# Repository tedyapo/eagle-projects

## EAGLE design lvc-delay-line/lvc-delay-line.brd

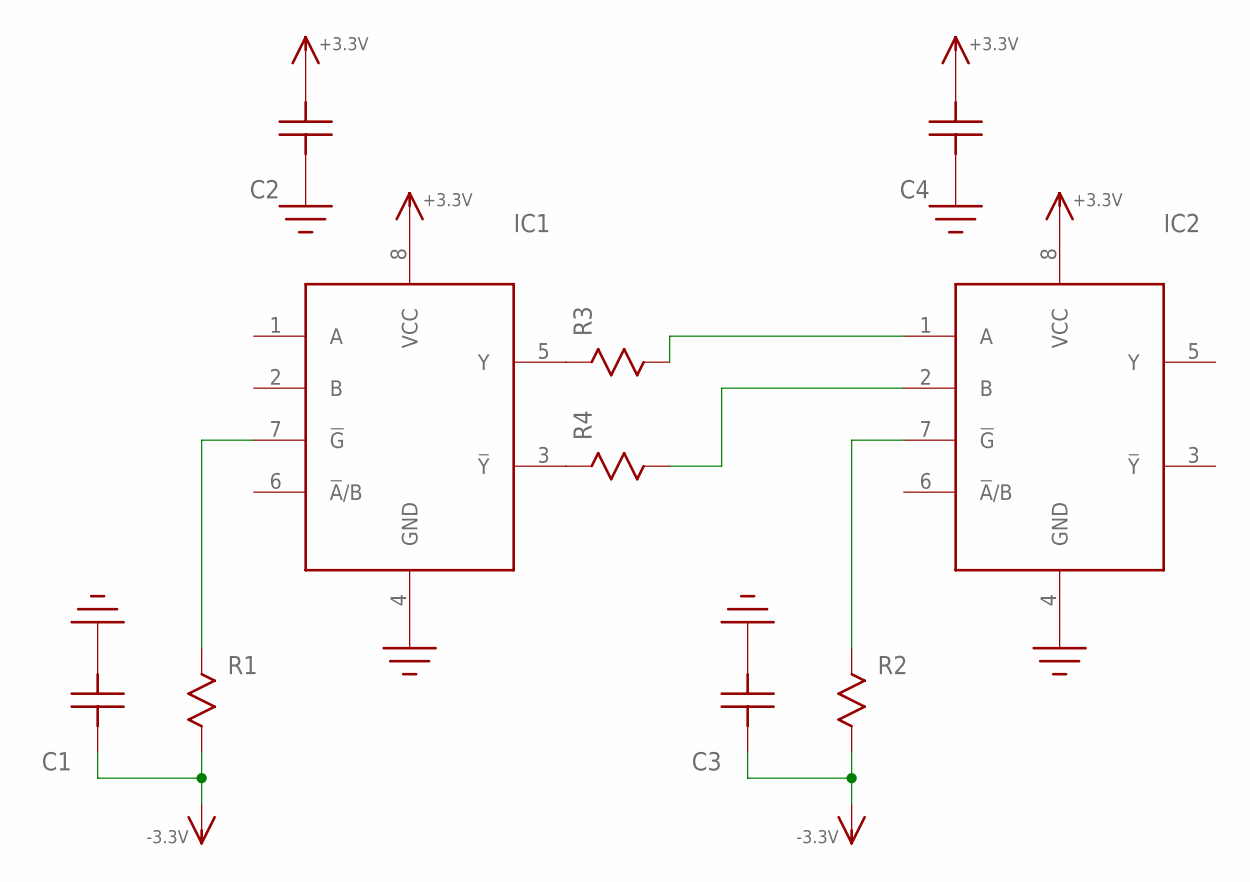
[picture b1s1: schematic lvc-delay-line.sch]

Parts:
C1, C2, C3, C4: C0603
IC1, IC2: 74LVC2G157; SSOP8
R1, R2: R0603
R3, R4: R0402; 0402

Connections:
+3.3V: C2.P$1, C4.P$1, IC1.8 (VCC), IC2.8 (VCC)
-3.3V: C1.P$2, C3.P$2, R1.P$2, R2.P$2
GND: C1.P$1, C2.P$2, C3.P$1, C4.P$2, IC1.4 (GND), IC2.4 (GND)
unnamed: IC1.7 (!G!), R1.P$1
unnamed: IC2.7 (!G!), R2.P$1
unnamed: IC2.1 (A), R3.2
unnamed: IC2.2 (B), R4.2
unnamed: IC1.5 (Y), R3.1
unnamed: IC1.3 (!Y!), R4.1

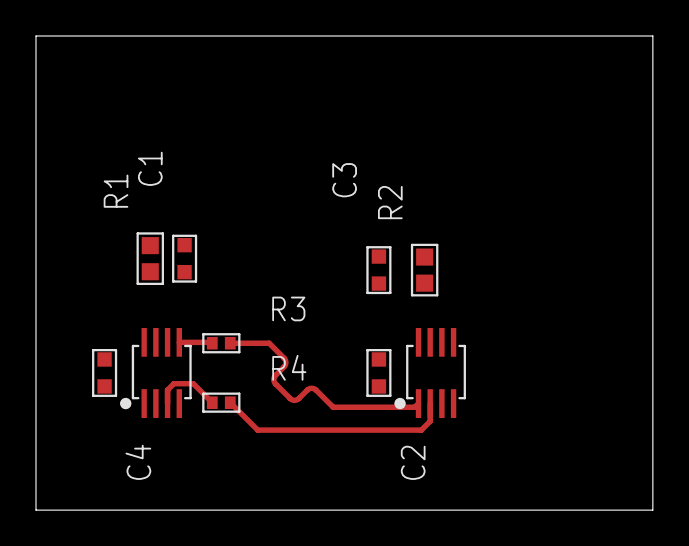
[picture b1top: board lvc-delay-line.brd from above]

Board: 2 copper layers, 34.3 x 26.3 mm, 10 parts (0 on the bottom side), 9 nets.

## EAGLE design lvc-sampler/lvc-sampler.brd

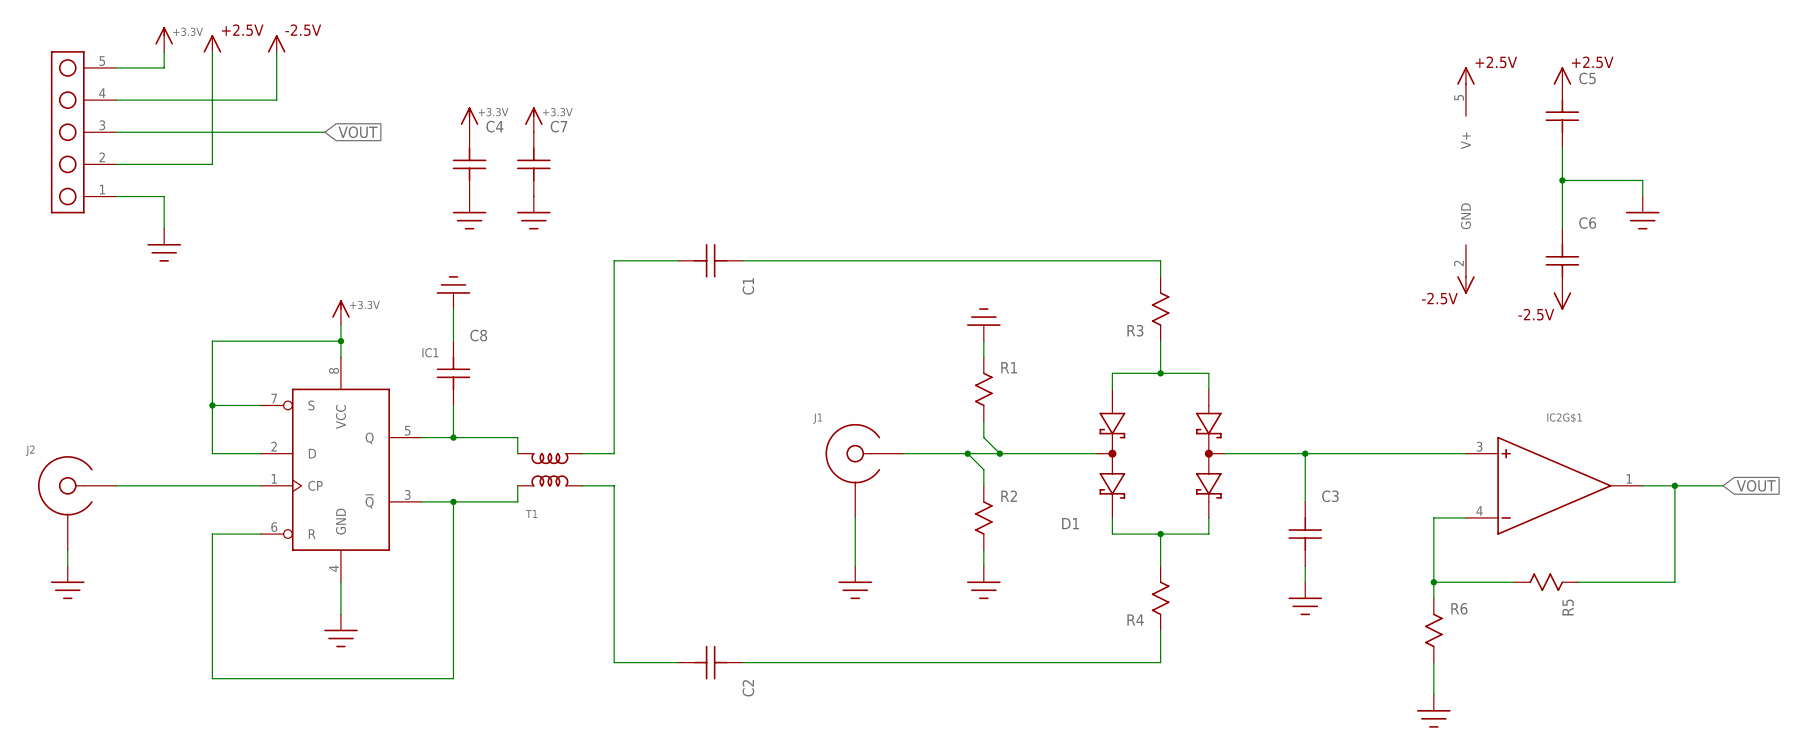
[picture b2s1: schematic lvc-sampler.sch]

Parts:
C1, C2, C3, C4, C5, C6, C7, C8: C0603
D1: SMS3923-081; SC-88
IC1: 74LVC2G74; SSOP8
IC2: MCP601; SOT23-5
J1, J2: SMA-EDGE-LAUNCH4020_TAPER; SMA_EDGE_LAUNCH_2L_4020_TAPER
J3: HEADER_5PIN
R1, R2, R3, R4, R5, R6: R0603
T1: MABA007159; MABAES0061

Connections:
+2.5V: C5.P$2, IC2.5 (V+), J3.2
+3.3V: C4.P$2, C7.P$2, IC1.2 (D), IC1.7 (S), IC1.8 (VCC), J3.5
-2.5V: C6.P$1, IC2.2 (GND), J3.4
GND: C3.P$1, C4.P$1, C5.P$1, C6.P$2, C7.P$1, C8.P$2, IC1.4 (GND), J1.BOTTOM_GND (SHIELD), J1.GND@1 (SHIELD), J1.GND@2 (SHIELD), J1.GND@3 (SHIELD), J1.GND@4 (SHIELD), J1.GND@5 (SHIELD), J1.GND@6 (SHIELD), J1.GND@7 (SHIELD), J1.GND@8 (SHIELD), J1.GND@14 (SHIELD), J1.GND@15 (SHIELD), J1.GND@16 (SHIELD), J1.GND@17 (SHIELD), J1.GND_PAD1 (SHIELD), J1.GND_PAD2 (SHIELD), J1.P$1 (SHIELD), J1.P$2 (SHIELD), J2.BOTTOM_GND (SHIELD), J2.GND@1 (SHIELD), J2.GND@2 (SHIELD), J2.GND@3 (SHIELD), J2.GND@4 (SHIELD), J2.GND@5 (SHIELD), J2.GND@6 (SHIELD), J2.GND@7 (SHIELD), J2.GND@8 (SHIELD), J2.GND@14 (SHIELD), J2.GND@15 (SHIELD), J2.GND@16 (SHIELD), J2.GND@17 (SHIELD), J2.GND_PAD1 (SHIELD), J2.GND_PAD2 (SHIELD), J2.P$1 (SHIELD), J2.P$2 (SHIELD), J3.1, R1.P$1, R2.P$2, R6.P$2
unnamed: IC1.3 (!Q!), IC1.6 (R), T1.5
unnamed: D1.2 (COMMON0), J1.CENTER@1 (CENTER), R1.P$2, R2.P$1
unnamed: D1.1 (ANODE0), D1.6 (ANODE1), R3.P$1
unnamed: D1.3 (CATHODE0), D1.4 (CATHODE1), R4.P$2
unnamed: C1.P$2, R3.P$2
unnamed: C2.P$2, R4.P$1
unnamed: C1.P$1, T1.3
unnamed: C2.P$1, T1.1
unnamed: C8.P$1, IC1.5 (Q), T1.4
unnamed: IC1.1 (CP), J2.CENTER@1 (CENTER)
unnamed: C3.P$2, D1.5 (COMMON1), IC2.3 (+)
unnamed: IC2.4 (-), R5.P$2, R6.P$1
VOUT: IC2.1 (OUT), J3.3, R5.P$1

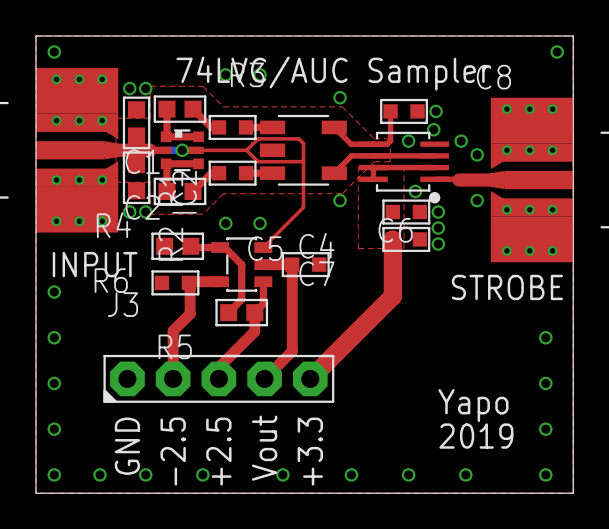
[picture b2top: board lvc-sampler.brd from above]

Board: 2 copper layers, 29.8 x 25.4 mm, 21 parts (1 on the bottom side), 17 nets.

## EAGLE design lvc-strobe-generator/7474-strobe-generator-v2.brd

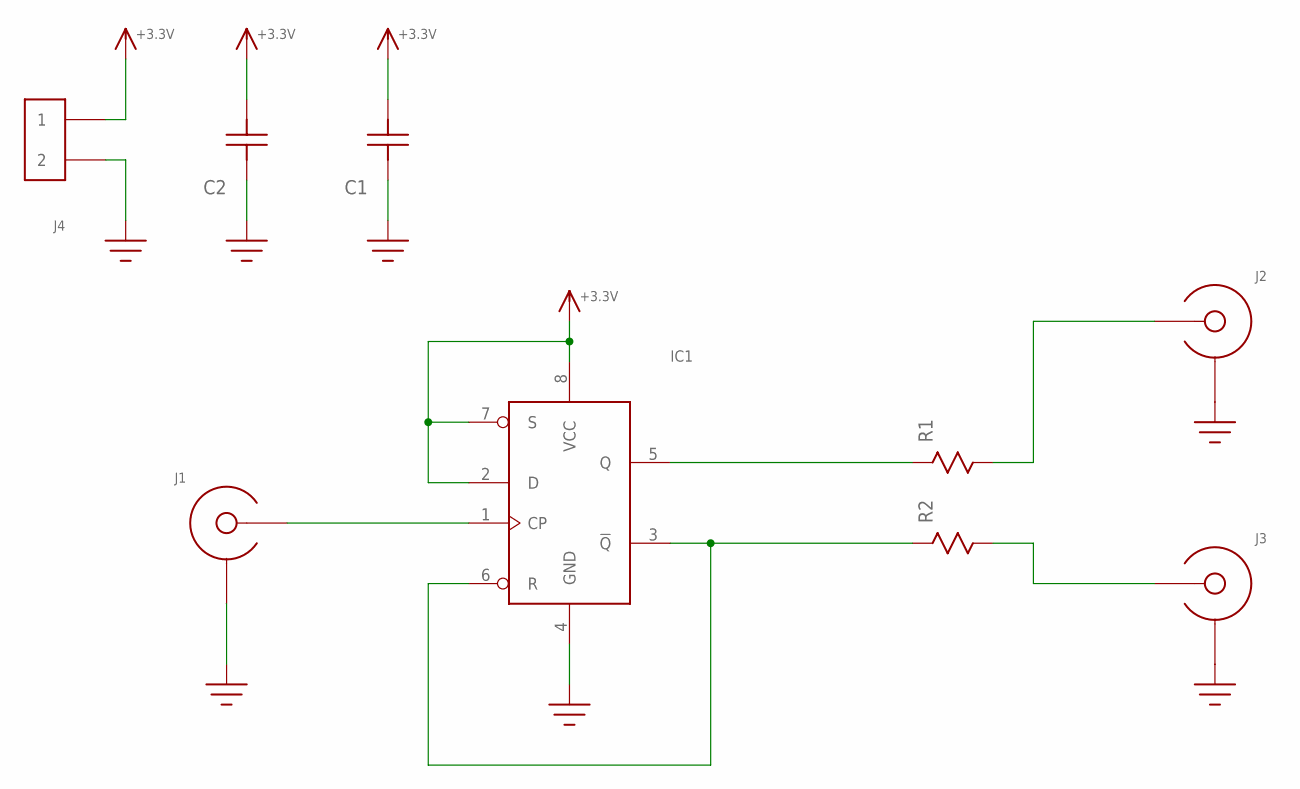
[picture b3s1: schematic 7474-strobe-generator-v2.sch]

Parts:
C1: C0603
C2: C1206; 1206
IC1: 74LVC2G74; SSOP8
J1, J2, J3: SMA-EDGE-LAUNCH4020_TAPER; SMA_EDGE_LAUNCH_2L_4020_TAPER
J4: HEADER_2PIN
R1, R2: R0603

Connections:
+3.3V: C1.P$1, C2.P$1, IC1.2 (D), IC1.7 (S), IC1.8 (VCC), J4.1
GND: C1.P$2, C2.P$2, IC1.4 (GND), J1.BOTTOM_GND (SHIELD), J1.GND@1 (SHIELD), J1.GND@2 (SHIELD), J1.GND@3 (SHIELD), J1.GND@4 (SHIELD), J1.GND@5 (SHIELD), J1.GND@6 (SHIELD), J1.GND@7 (SHIELD), J1.GND@8 (SHIELD), J1.GND@14 (SHIELD), J1.GND@15 (SHIELD), J1.GND@16 (SHIELD), J1.GND@17 (SHIELD), J1.GND_PAD1 (SHIELD), J1.GND_PAD2 (SHIELD), J1.P$1 (SHIELD), J1.P$2 (SHIELD), J2.BOTTOM_GND (SHIELD), J2.GND@1 (SHIELD), J2.GND@2 (SHIELD), J2.GND@3 (SHIELD), J2.GND@4 (SHIELD), J2.GND@5 (SHIELD), J2.GND@6 (SHIELD), J2.GND@7 (SHIELD), J2.GND@8 (SHIELD), J2.GND@14 (SHIELD), J2.GND@15 (SHIELD), J2.GND@16 (SHIELD), J2.GND@17 (SHIELD), J2.GND_PAD1 (SHIELD), J2.GND_PAD2 (SHIELD), J2.P$1 (SHIELD), J2.P$2 (SHIELD), J3.BOTTOM_GND (SHIELD), J3.GND@1 (SHIELD), J3.GND@2 (SHIELD), J3.GND@3 (SHIELD), J3.GND@4 (SHIELD), J3.GND@5 (SHIELD), J3.GND@6 (SHIELD), J3.GND@7 (SHIELD), J3.GND@8 (SHIELD), J3.GND@14 (SHIELD), J3.GND@15 (SHIELD), J3.GND@16 (SHIELD), J3.GND@17 (SHIELD), J3.GND_PAD1 (SHIELD), J3.GND_PAD2 (SHIELD), J3.P$1 (SHIELD), J3.P$2 (SHIELD), J4.2
unnamed: IC1.1 (CP), J1.CENTER@1 (CENTER)
unnamed: IC1.3 (!Q!), IC1.6 (R), R2.P$1
unnamed: J2.CENTER@1 (CENTER), R1.P$2
unnamed: IC1.5 (Q), R1.P$1
unnamed: J3.CENTER@1 (CENTER), R2.P$2

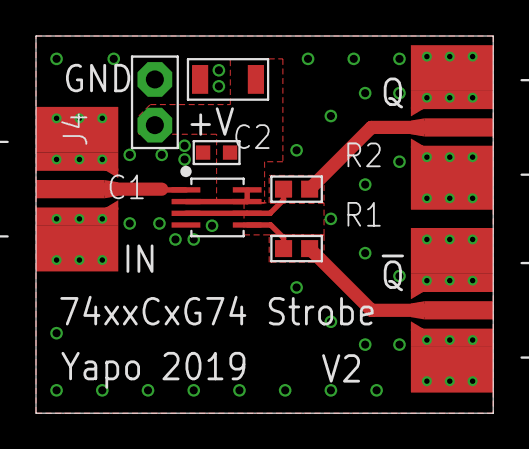
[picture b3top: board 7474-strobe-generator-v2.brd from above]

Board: 2 copper layers, 25.4 x 21.0 mm, 9 parts (0 on the bottom side), 7 nets.

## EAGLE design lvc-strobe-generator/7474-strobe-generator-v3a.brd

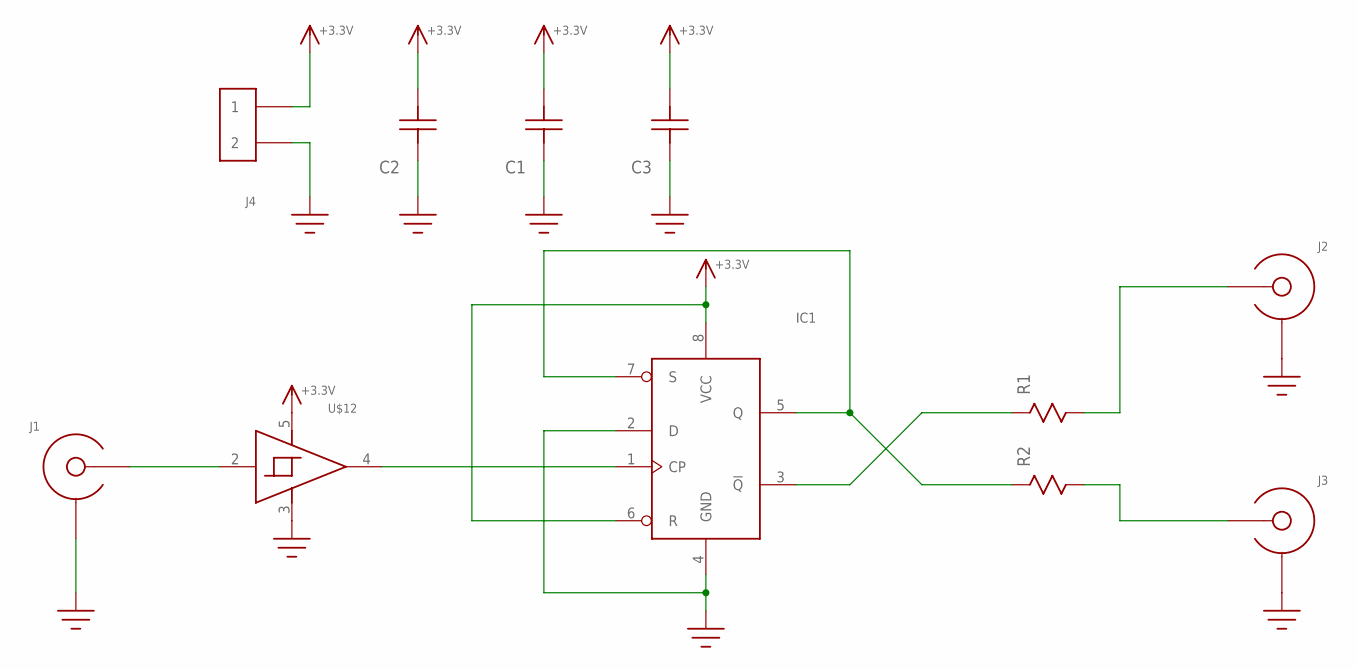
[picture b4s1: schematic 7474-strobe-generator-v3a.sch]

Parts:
C1, C3: C0603
C2: C1206; 1206
IC1: 74LVC2G74; SSOP8
J1, J2, J3: SMA-EDGE-LAUNCH4020_TAPER; SMA_EDGE_LAUNCH_2L_4020_TAPER
J4: HEADER_2PIN
R1, R2: R0603
U$12: 74LVC1G17; SOT23-5

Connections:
+3.3V: C1.P$1, C2.P$1, C3.P$1, IC1.6 (R), IC1.8 (VCC), J4.1, U$12.5 (VCC)
GND: C1.P$2, C2.P$2, C3.P$2, IC1.2 (D), IC1.4 (GND), J1.BOTTOM_GND (SHIELD), J1.GND@1 (SHIELD), J1.GND@2 (SHIELD), J1.GND@3 (SHIELD), J1.GND@4 (SHIELD), J1.GND@5 (SHIELD), J1.GND@6 (SHIELD), J1.GND@7 (SHIELD), J1.GND@8 (SHIELD), J1.GND@14 (SHIELD), J1.GND@15 (SHIELD), J1.GND@16 (SHIELD), J1.GND@17 (SHIELD), J1.GND_PAD1 (SHIELD), J1.GND_PAD2 (SHIELD), J1.P$1 (SHIELD), J1.P$2 (SHIELD), J2.BOTTOM_GND (SHIELD), J2.GND@1 (SHIELD), J2.GND@2 (SHIELD), J2.GND@3 (SHIELD), J2.GND@4 (SHIELD), J2.GND@5 (SHIELD), J2.GND@6 (SHIELD), J2.GND@7 (SHIELD), J2.GND@8 (SHIELD), J2.GND@14 (SHIELD), J2.GND@15 (SHIELD), J2.GND@16 (SHIELD), J2.GND@17 (SHIELD), J2.GND_PAD1 (SHIELD), J2.GND_PAD2 (SHIELD), J2.P$1 (SHIELD), J2.P$2 (SHIELD), J3.BOTTOM_GND (SHIELD), J3.GND@1 (SHIELD), J3.GND@2 (SHIELD), J3.GND@3 (SHIELD), J3.GND@4 (SHIELD), J3.GND@5 (SHIELD), J3.GND@6 (SHIELD), J3.GND@7 (SHIELD), J3.GND@8 (SHIELD), J3.GND@14 (SHIELD), J3.GND@15 (SHIELD), J3.GND@16 (SHIELD), J3.GND@17 (SHIELD), J3.GND_PAD1 (SHIELD), J3.GND_PAD2 (SHIELD), J3.P$1 (SHIELD), J3.P$2 (SHIELD), J4.2, U$12.3 (GND)
unnamed: IC1.1 (CP), U$12.4 (OUT)
unnamed: IC1.3 (!Q!), R1.P$1
unnamed: J2.CENTER@1 (CENTER), R1.P$2
unnamed: J3.CENTER@1 (CENTER), R2.P$2
unnamed: J1.CENTER@1 (CENTER), U$12.2 (IN)
unnamed: IC1.5 (Q), IC1.7 (S), R2.P$1

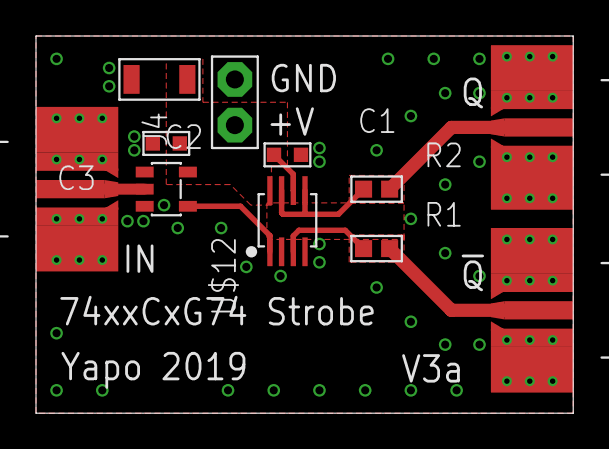
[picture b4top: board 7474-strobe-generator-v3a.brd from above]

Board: 2 copper layers, 29.8 x 21.0 mm, 11 parts (0 on the bottom side), 8 nets.

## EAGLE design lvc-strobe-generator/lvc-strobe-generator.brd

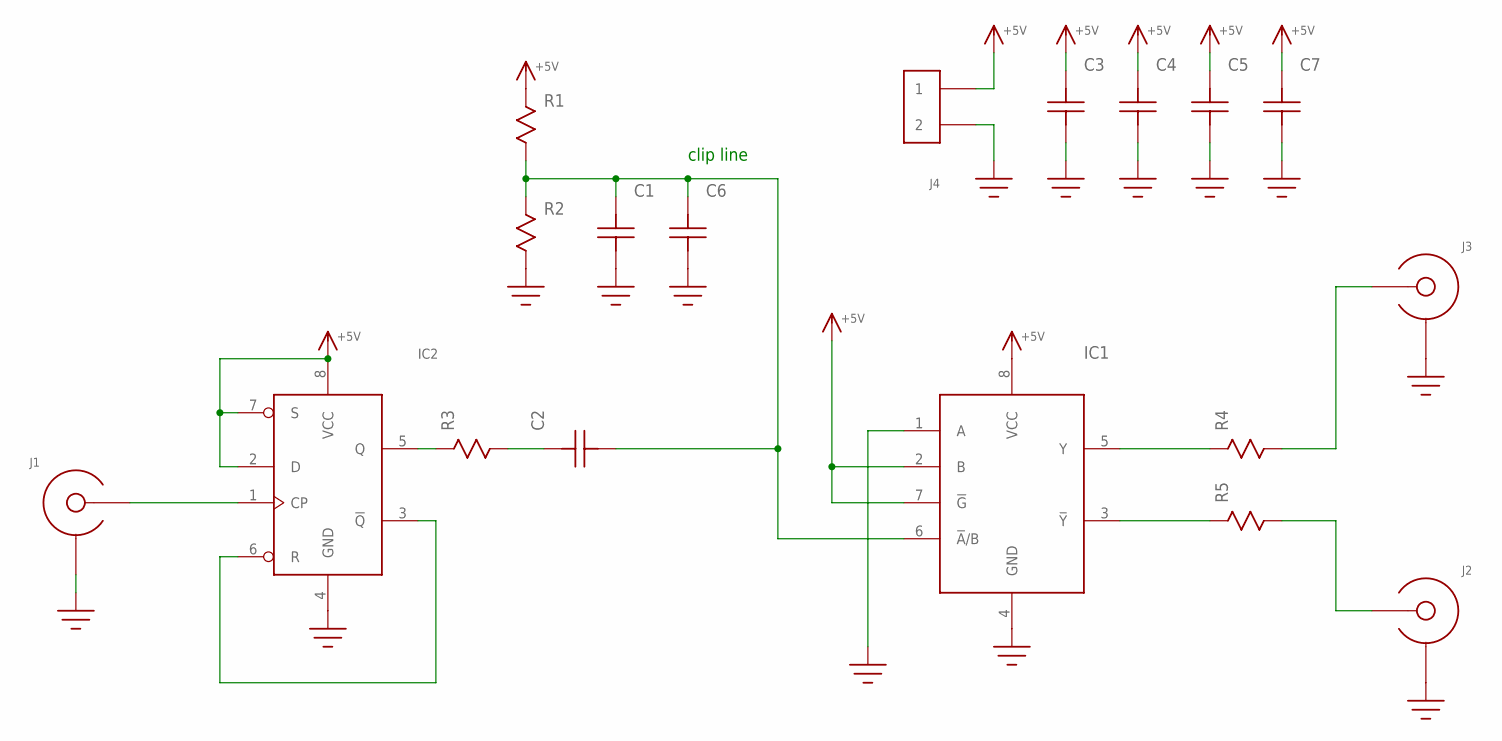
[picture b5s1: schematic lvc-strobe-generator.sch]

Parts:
C1, C2, C6: C; C0402
C3: C1206; 1206
C4, C5, C7: C0603
IC1: 74LVC2G157; SSOP8
IC2: 74LVC2G74; SSOP8
J1, J2, J3: SMA-EDGE-LAUNCH4L-4020-TAPER-FIXED; SMA_EDGE_LAUNCH_4L_4020_TAPER_FIXED
J4: HEADER_2PIN
R1, R2, R4, R5: R0603
R3: R0402; 0402

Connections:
+5V: C3.P$2, C4.P$2, C5.P$2, C7.P$2, IC1.2 (B), IC1.7 (!G!), IC1.8 (VCC), IC2.2 (D), IC2.7 (S), IC2.8 (VCC), J4.1, R1.P$1
GND: C1.1, C3.P$1, C4.P$1, C5.P$1, C6.1, C7.P$1, IC1.1 (A), IC1.4 (GND), IC2.4 (GND), J1.BOTTOM_GND (SHIELD), J1.GND@1 (SHIELD), J1.GND@2 (SHIELD), J1.GND@3 (SHIELD), J1.GND@4 (SHIELD), J1.GND@5 (SHIELD), J1.GND@6 (SHIELD), J1.GND@7 (SHIELD), J1.GND@8 (SHIELD), J1.GND@14 (SHIELD), J1.GND@15 (SHIELD), J1.GND@16 (SHIELD), J1.GND@17 (SHIELD), J1.GND_PAD1 (SHIELD), J1.GND_PAD2 (SHIELD), J1.P$1 (SHIELD), J1.P$2 (SHIELD), J2.BOTTOM_GND (SHIELD), J2.GND@1 (SHIELD), J2.GND@2 (SHIELD), J2.GND@3 (SHIELD), J2.GND@4 (SHIELD), J2.GND@5 (SHIELD), J2.GND@6 (SHIELD), J2.GND@7 (SHIELD), J2.GND@8 (SHIELD), J2.GND@14 (SHIELD), J2.GND@15 (SHIELD), J2.GND@16 (SHIELD), J2.GND@17 (SHIELD), J2.GND_PAD1 (SHIELD), J2.GND_PAD2 (SHIELD), J2.P$1 (SHIELD), J2.P$2 (SHIELD), J3.BOTTOM_GND (SHIELD), J3.GND@1 (SHIELD), J3.GND@2 (SHIELD), J3.GND@3 (SHIELD), J3.GND@4 (SHIELD), J3.GND@5 (SHIELD), J3.GND@6 (SHIELD), J3.GND@7 (SHIELD), J3.GND@8 (SHIELD), J3.GND@14 (SHIELD), J3.GND@15 (SHIELD), J3.GND@16 (SHIELD), J3.GND@17 (SHIELD), J3.GND_PAD1 (SHIELD), J3.GND_PAD2 (SHIELD), J3.P$1 (SHIELD), J3.P$2 (SHIELD), J4.2, R2.P$2
unnamed: IC2.5 (Q), R3.1
unnamed: C1.2, C2.1, C6.2, IC1.6 (!A!/B), R1.P$2, R2.P$1
unnamed: IC2.3 (!Q!), IC2.6 (R)
unnamed: C2.2, R3.2
unnamed: IC1.5 (Y), R4.P$1
unnamed: IC1.3 (!Y!), R5.P$1
unnamed: IC2.1 (CP), J1.CENTER@1 (CENTER), J1.P$3 (CENTER)
unnamed: J3.CENTER@1 (CENTER), J3.P$3 (CENTER), R4.P$2
unnamed: J2.CENTER@1 (CENTER), J2.P$3 (CENTER), R5.P$2

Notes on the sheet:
clip line

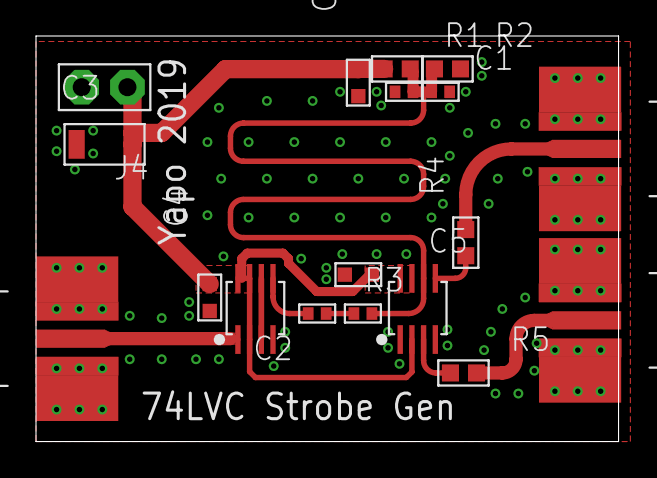
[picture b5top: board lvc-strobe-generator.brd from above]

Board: 2 copper layers, 32.4 x 22.5 mm, 18 parts (0 on the bottom side), 11 nets.

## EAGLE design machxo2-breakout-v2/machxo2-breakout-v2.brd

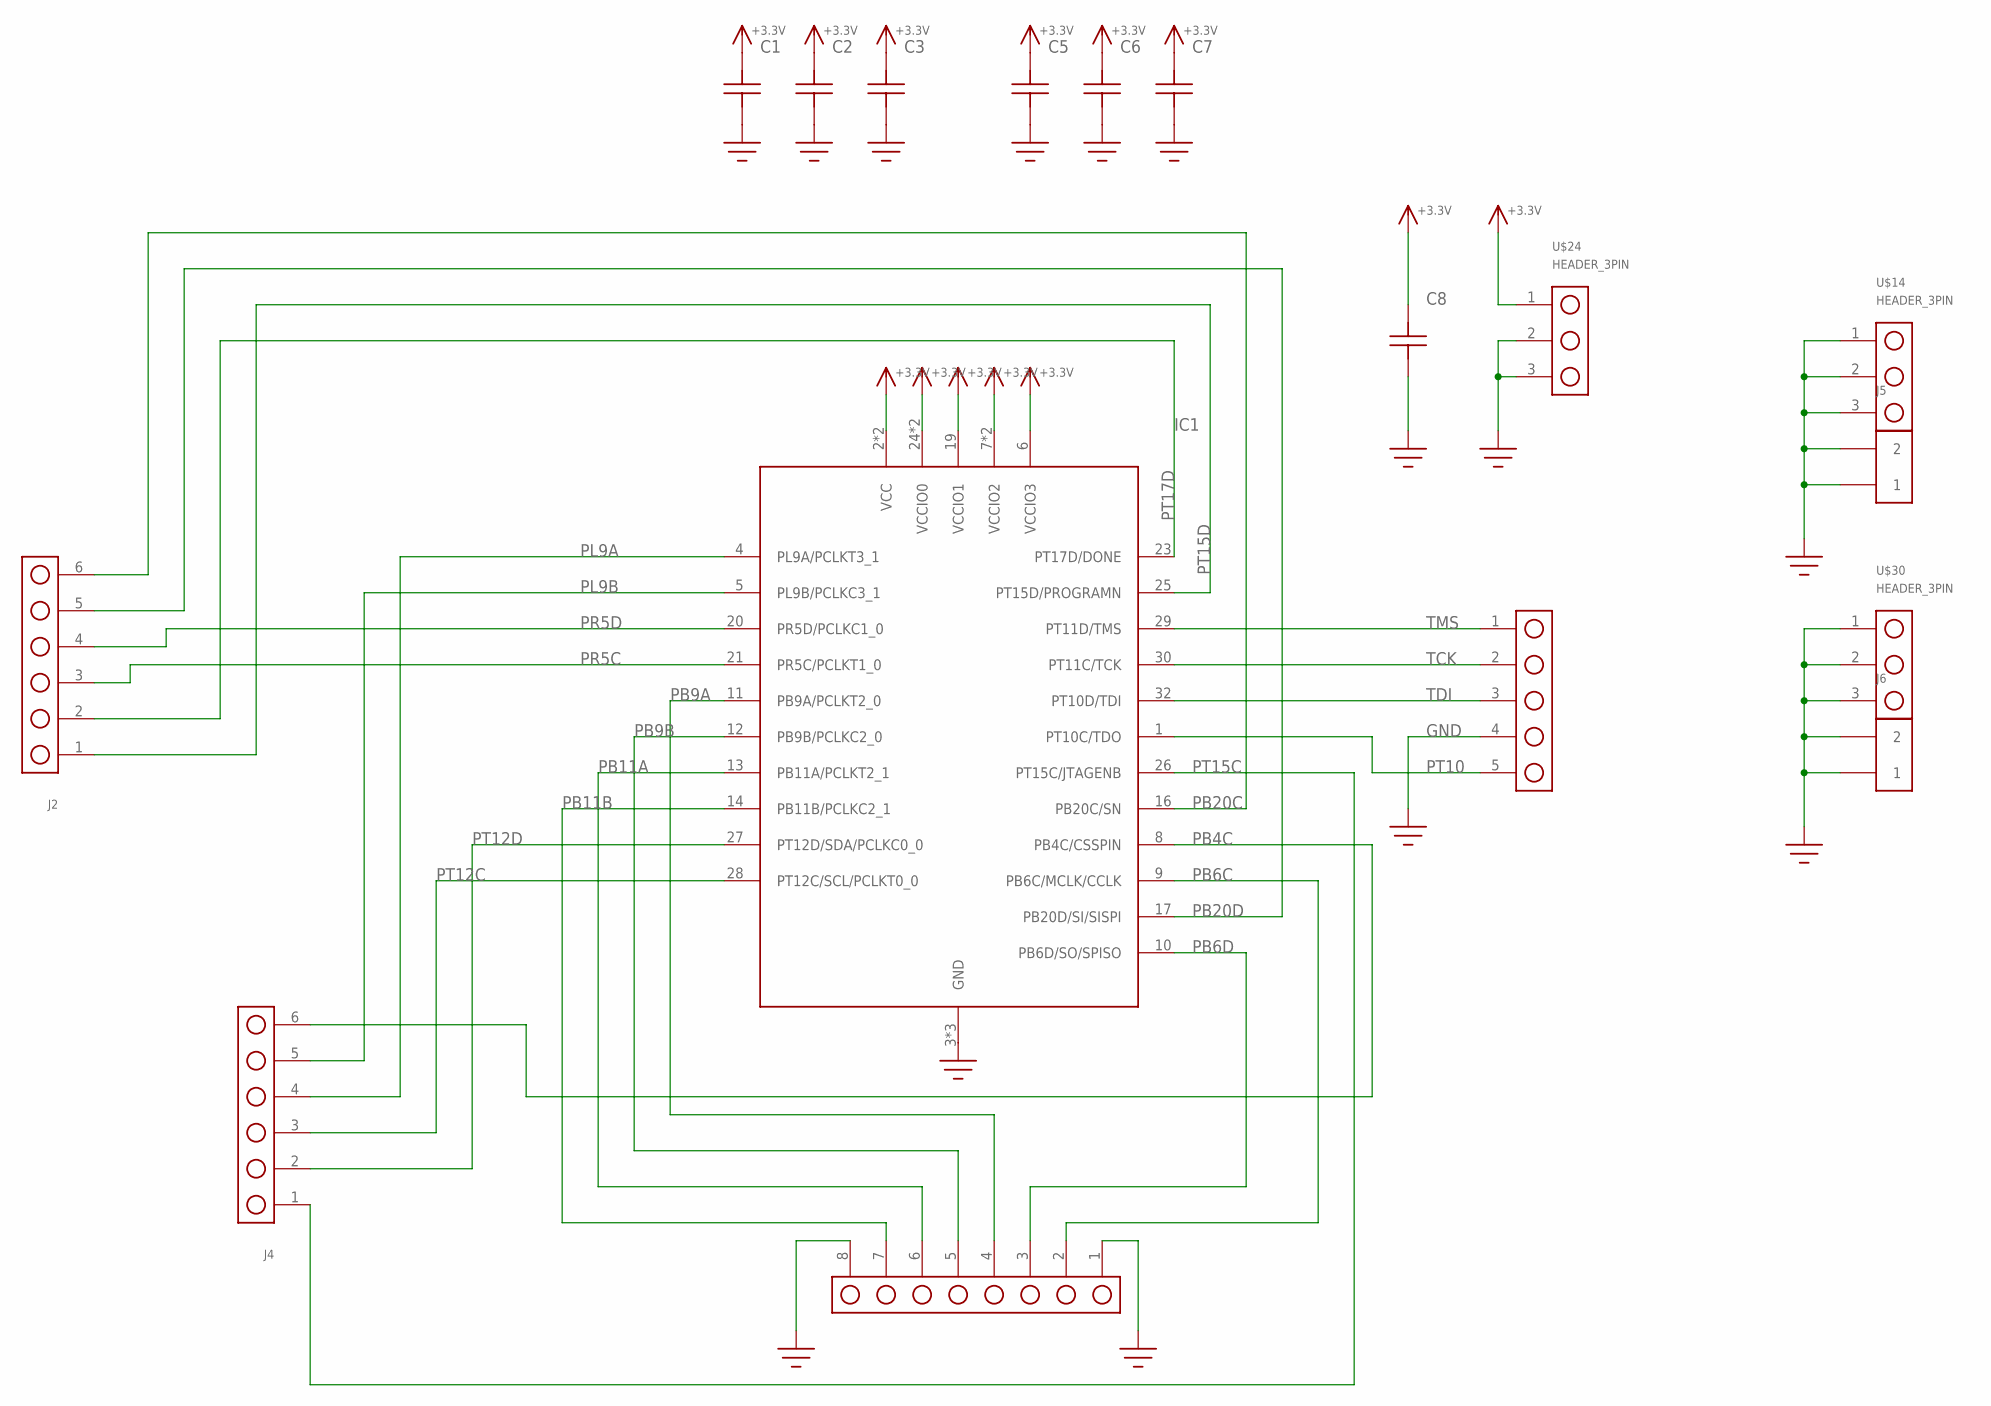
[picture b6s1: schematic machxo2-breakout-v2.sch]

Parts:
C1, C2, C3, C5, C6, C7: C; C0402
C8: C1206; 1206
IC1: MACHXO2_1200EXTENDED; QFN32_5X5-EXTENDED
J1: HEADER_5PIN
J2, J4: HEADER_6PIN
J3: HEADER_8PIN; HEADER_8_PIN
J5, J6: HEADER_2PIN
U$14, U$24, U$30: HEADER_3PIN

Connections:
+3.3V: C1.2, C2.2, C3.2, C5.2, C6.2, C7.2, C8.P$2, IC1.2 (VCC), IC1.6 (VCCIO3), IC1.7 (VCCIO2), IC1.15 (VCCIO2), IC1.18 (VCC), IC1.19 (VCCIO1), IC1.24 (VCCIO0), IC1.31 (VCCIO0), U$24.1
GND: C1.1, C2.1, C3.1, C5.1, C6.1, C7.1, C8.P$1, IC1.3 (GND), IC1.22 (GND), IC1.PAD (GND), J1.4, J3.1, J3.8, J5.1, J5.2, J6.1, J6.2, U$14.1, U$14.2, U$14.3, U$24.2, U$24.3, U$30.1, U$30.2, U$30.3
PB4C: IC1.8 (PB4C/CSSPIN), J4.6
PB6C: IC1.9 (PB6C/MCLK/CCLK), J3.2
PB6D: IC1.10 (PB6D/SO/SPISO), J3.3
PB9A: IC1.11 (PB9A/PCLKT2_0), J3.4
PB9B: IC1.12 (PB9B/PCLKC2_0), J3.5
PB11A: IC1.13 (PB11A/PCLKT2_1), J3.6
PB11B: IC1.14 (PB11B/PCLKC2_1), J3.7
PB20C: IC1.16 (PB20C/SN), J2.6
PB20D: IC1.17 (PB20D/SI/SISPI), J2.5
PL9A: IC1.4 (PL9A/PCLKT3_1), J4.4
PL9B: IC1.5 (PL9B/PCLKC3_1), J4.5
PR5C: IC1.21 (PR5C/PCLKT1_0), J2.3
PR5D: IC1.20 (PR5D/PCLKC1_0), J2.4
PT10: IC1.1 (PT10C/TDO), J1.5
PT12C: IC1.28 (PT12C/SCL/PCLKT0_0), J4.3
PT12D: IC1.27 (PT12D/SDA/PCLKC0_0), J4.2
PT15C: IC1.26 (PT15C/JTAGENB), J4.1
PT15D: IC1.25 (PT15D/PROGRAMN), J2.1
PT17D: IC1.23 (PT17D/DONE), J2.2
TCK: IC1.30 (PT11C/TCK), J1.2
TDI: IC1.32 (PT10D/TDI), J1.3
TMS: IC1.29 (PT11D/TMS), J1.1

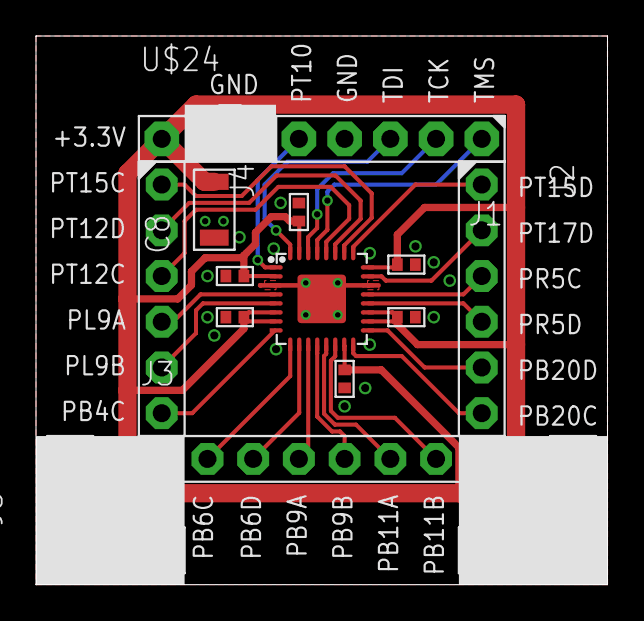
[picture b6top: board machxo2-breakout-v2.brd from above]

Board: 2 copper layers, 31.8 x 30.5 mm, 17 parts (0 on the bottom side), 24 nets.

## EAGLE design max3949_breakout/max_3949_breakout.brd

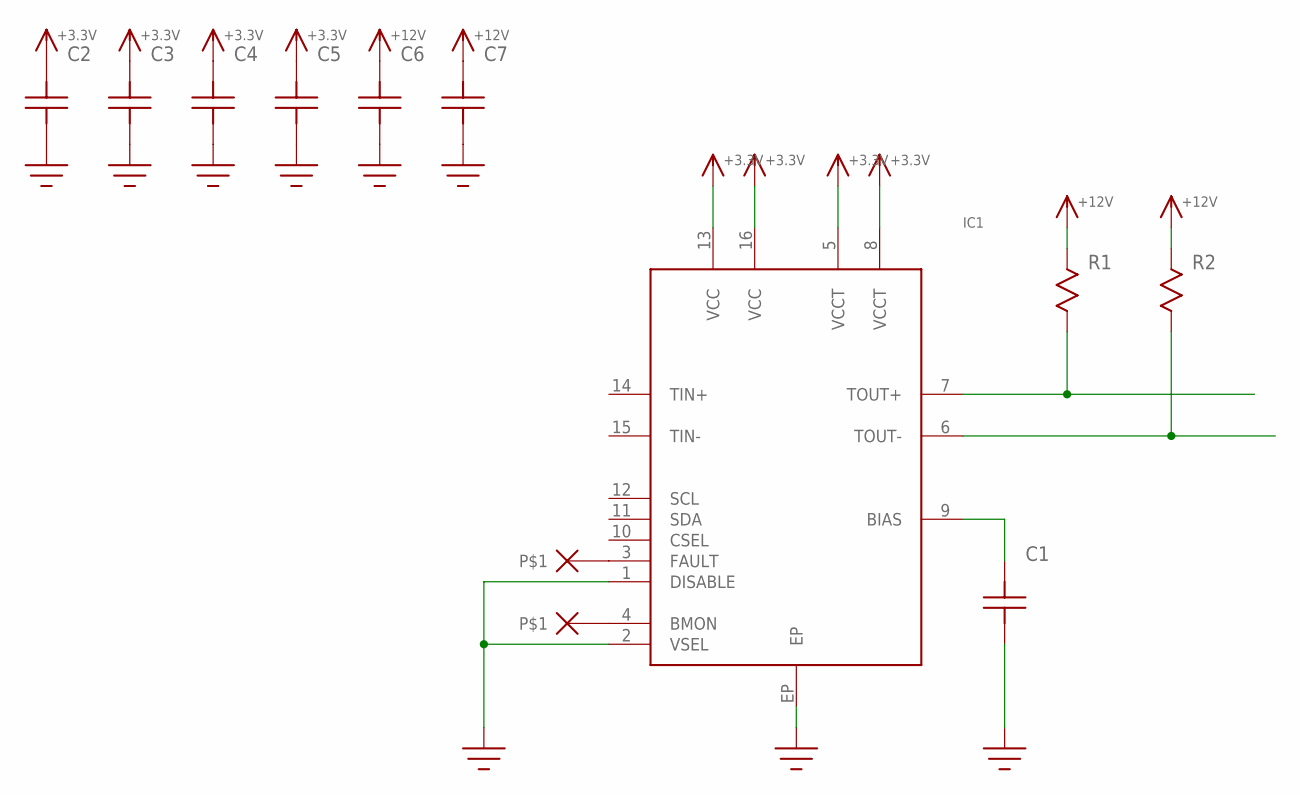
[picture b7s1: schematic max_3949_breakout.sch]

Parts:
C1, C2, C3, C4, C5, C6, C7: C0603
IC1: MAX3949; TQFN16
R1, R2: R1206

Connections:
+3.3V: C2.P$2, C3.P$2, C4.P$2, C5.P$2, IC1.5 (VCCT), IC1.8 (VCCT), IC1.13 (VCC), IC1.16 (VCC)
+12V: C6.P$2, C7.P$2, R1.P$1, R2.P$1
GND: C1.P$1, C2.P$1, C3.P$1, C4.P$1, C5.P$1, C6.P$1, C7.P$1, IC1.1 (DISABLE), IC1.2 (VSEL), IC1.EP
unnamed: C1.P$2, IC1.9 (BIAS)
unnamed: IC1.7 (TOUT+), R1.P$2
unnamed: IC1.6 (TOUT-), R2.P$2

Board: 2 copper layers, 10 parts (0 on the bottom side), 6 nets, no tracks yet.
